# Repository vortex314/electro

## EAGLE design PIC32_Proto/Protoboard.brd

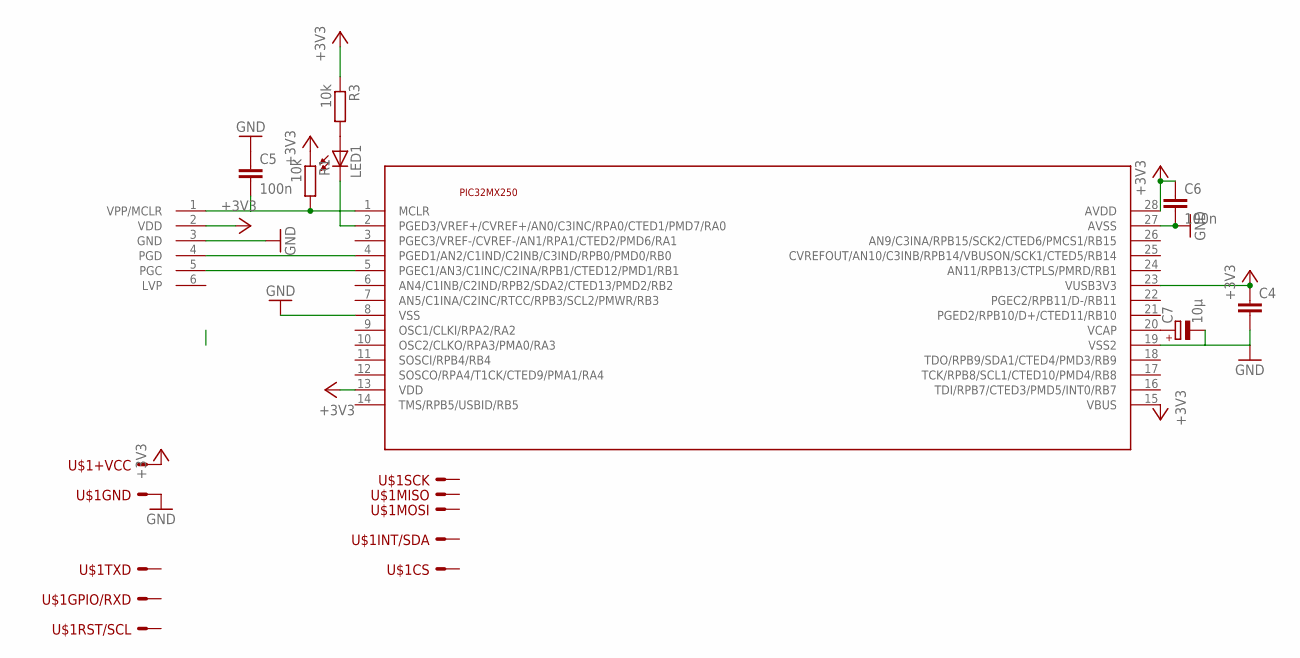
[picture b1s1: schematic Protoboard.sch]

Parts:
C4: C-EU050-025X075; C050-025X075
C5: 100n; C050-025X075
C6: 100n; C050-024X044
C7: 10µ; E1,8-4
LED1: LED5MM
R1, R3: 10k; 0207/10
U$1: SPI_BUS2
U$2: ICSP-6_6P; 1X06-CLEANBIG
U$3: PIC32MX2XXSOIC; SOIC28

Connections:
+3V3: C4.1, C6.1, R1.1, R3.1, U$1.+VCC, U$2.2 (VDD), U$3.13 (VDD), U$3.15 (VBUS), U$3.23 (VUSB3V3), U$3.28 (AVDD)
GND: C4.2, C5.1, C6.2, C7.-, U$1.GND, U$2.3 (GND), U$3.8 (VSS), U$3.19 (VSS2), U$3.27 (AVSS)
unnamed: C5.2, R1.2, U$2.1 (VPP/MCLR), U$3.1 (MCLR)
unnamed: U$2.5 (PGC), U$3.5 (PGEC1/AN3/C1INC/C2INA/RPB1/CTED12/PMD1/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)
unnamed: U$2.4 (PGD), U$3.4 (PGED1/AN2/C1IND/C2INB/C3IND/RPB0/PMD0/R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)
unnamed: LED1.K (C), U$3.2 (PGED3/VREF+/CVREF+/AN0/C3INC/RPA0/CTED1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)
unnamed: C7.+, U$3.20 (VCAP)
unnamed: LED1.A, R3.2

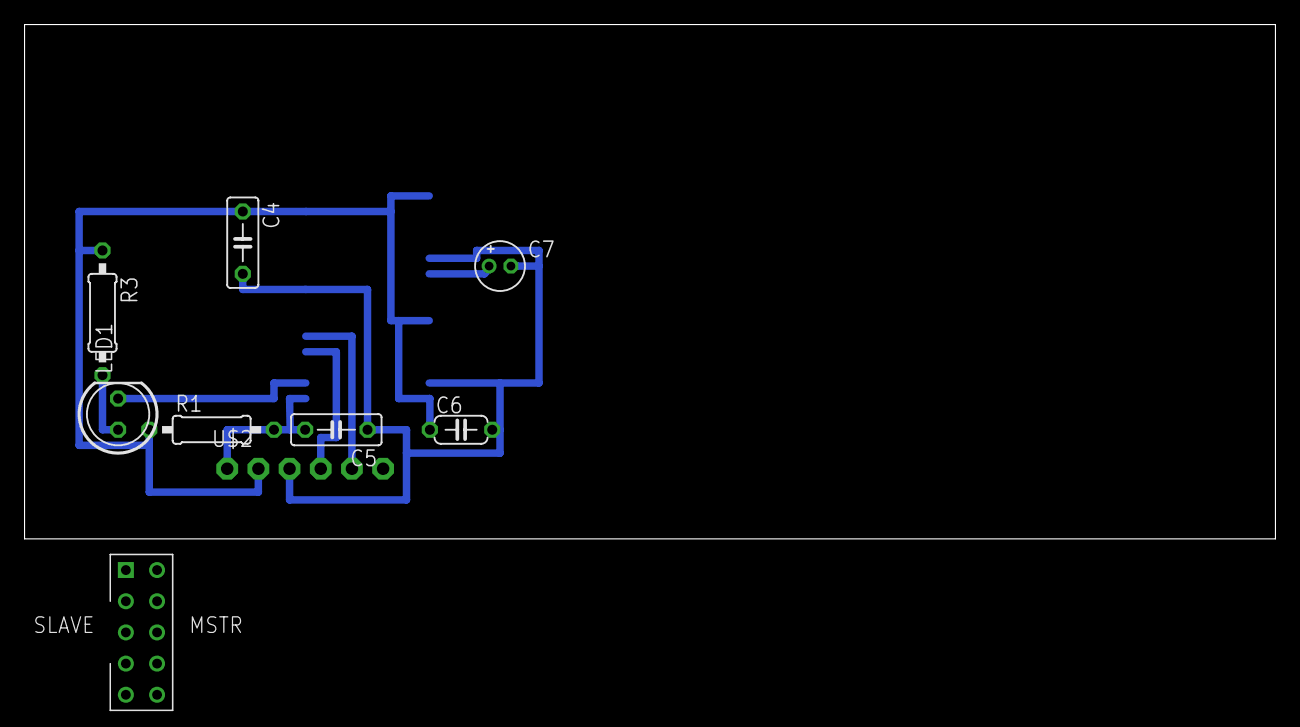
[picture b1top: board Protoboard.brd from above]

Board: 2 copper layers, 101.9 x 41.9 mm, 10 parts (1 on the bottom side), 8 nets.

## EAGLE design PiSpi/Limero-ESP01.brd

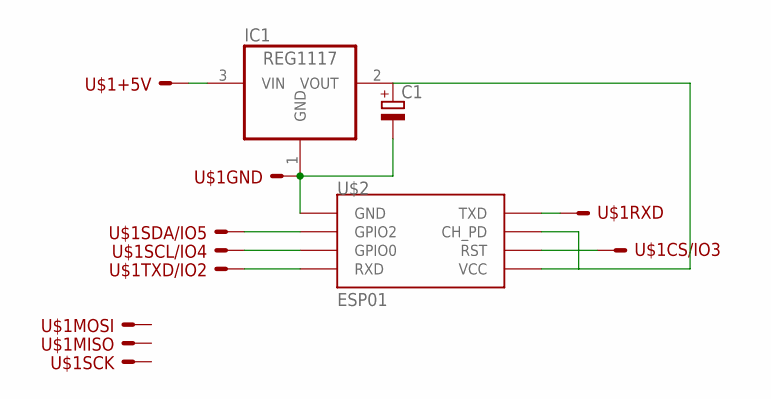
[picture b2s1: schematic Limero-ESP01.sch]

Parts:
C1: CPOL-EUB45181A; B45181A
IC1: REG1117; SOT223
U$1: LIMERO_BUS; SPI_BUS
U$2: ESP01

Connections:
unnamed: C1.-, IC1.1 (GND), U$1.GND, U$2.GND
unnamed: U$1.TXD, U$2.RX (RXD)
unnamed: U$1.RXD, U$2.TX (TXD)
unnamed: U$1.CS, U$2.RST
unnamed: U$1.SCL, U$2.GPIO0
unnamed: U$1.SDA, U$2.GPIO2
unnamed: IC1.3 (VIN), U$1.+5V
unnamed: C1.+, IC1.2 (VOUT), U$2.CH_PD, U$2.VCC

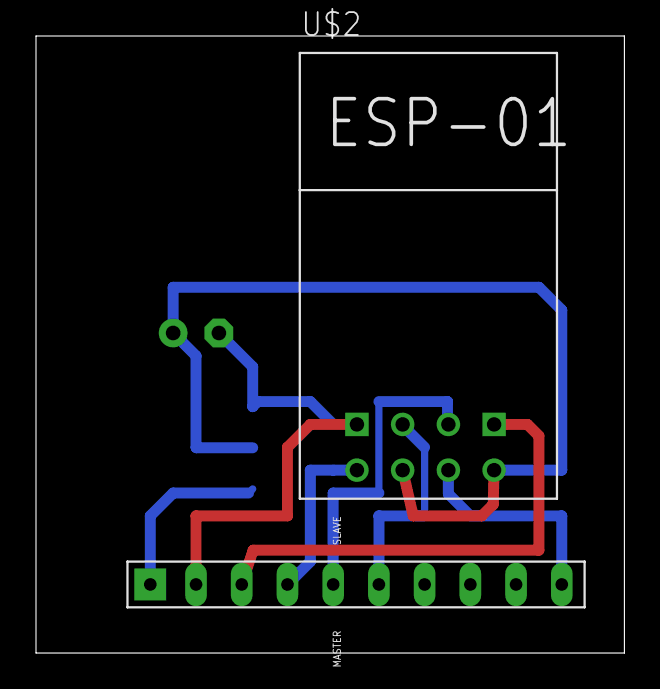
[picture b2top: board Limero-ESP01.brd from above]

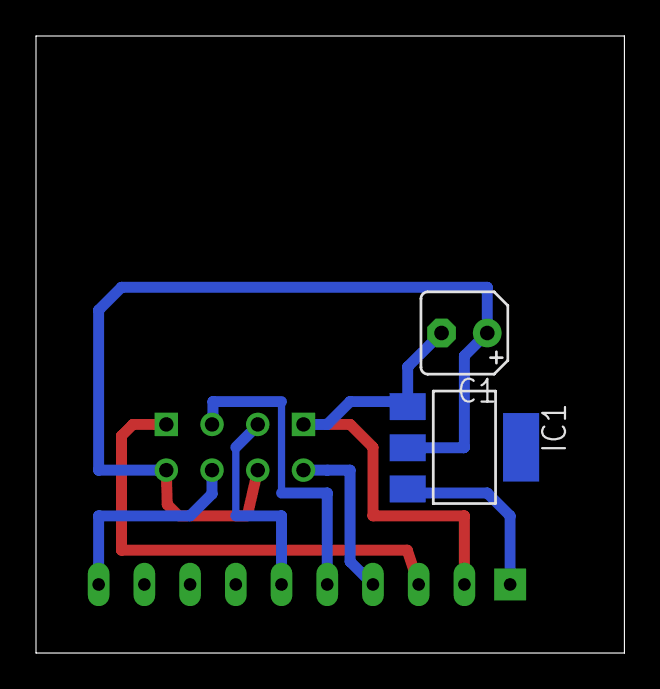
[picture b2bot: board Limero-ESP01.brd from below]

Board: 2 copper layers, 32.7 x 34.3 mm, 4 parts (2 on the bottom side), 8 nets.

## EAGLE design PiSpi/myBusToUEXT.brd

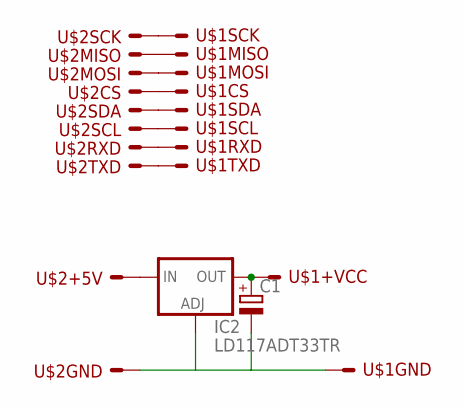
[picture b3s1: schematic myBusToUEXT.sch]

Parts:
C1: CPOL-EUE2.5-5; E2,5-5
IC2: LD117ADT33TR; DPACK
U$1: SPI_BUS2
U$2: SPI_BUS

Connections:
unnamed: U$1.TXD, U$2.TXD
unnamed: U$1.MOSI, U$2.MOSI
unnamed: U$1.MISO, U$2.MISO
unnamed: U$1.SCK, U$2.SCK
unnamed: U$1.CS, U$2.CS
unnamed: U$1.INT/SDA, U$2.SDA
unnamed: U$1.RST/SCL, U$2.SCL
unnamed: U$1.GPIO/RXD, U$2.RXD
unnamed: C1.-, IC2.1 (ADJ), U$1.GND, U$2.GND
unnamed: C1.+, IC2.4 (OUT), U$1.+VCC
unnamed: IC2.3 (IN), U$2.+5V

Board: 2 copper layers, 4 parts (1 on the bottom side), 11 nets, no tracks yet.

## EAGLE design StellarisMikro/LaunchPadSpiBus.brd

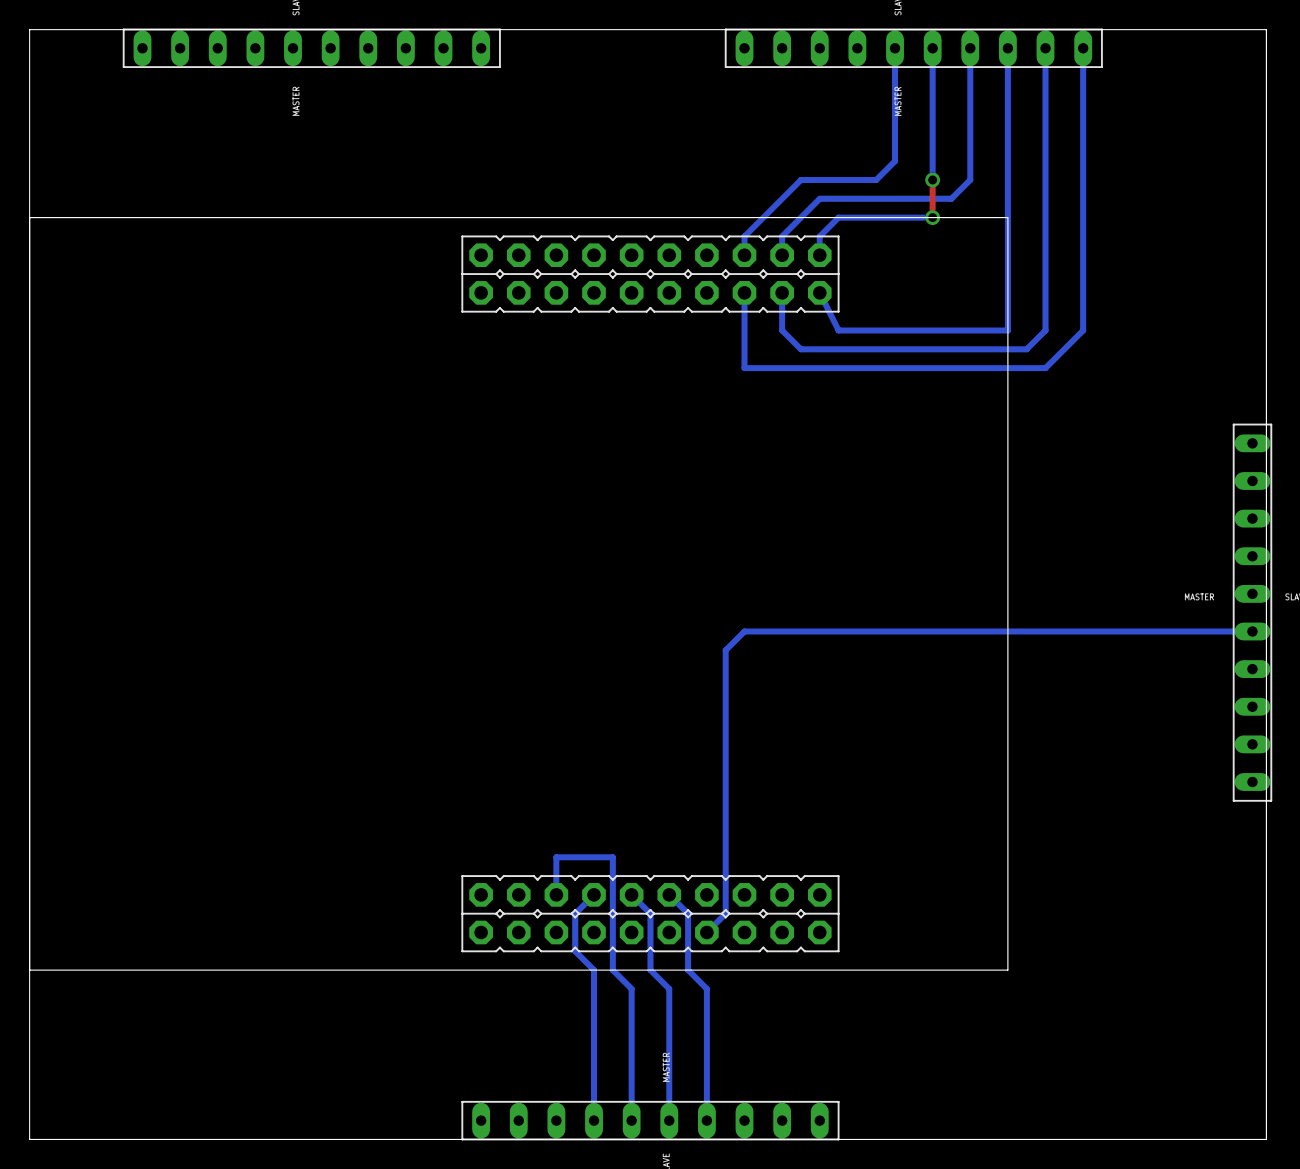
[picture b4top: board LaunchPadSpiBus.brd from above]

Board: 2 copper layers, 83.5 x 74.9 mm, 5 parts (0 on the bottom side), 22 nets.

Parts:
U$1: STELLARIS-LAUNCHPADSTELLARIS-LAUNCHPAD-XL; LAUNCHPAD-XL
U$2, U$3, U$4, U$5: SPI_BUS

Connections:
unnamed: U$1.PA3, U$2.CS
unnamed: U$1.PD0, U$3.SCK
unnamed: U$1.PD1, U$3.CS
unnamed: U$1.VBUS, U$2.+5V, U$3.+5V
unnamed: U$1.PA2, U$2.SCK
unnamed: U$1.GND1, U$1.GND2, U$2.GND, U$3.GND
unnamed: U$1.3.3V, U$2.+3V3, U$3.+3V3
unnamed: U$1.PB5, U$5.CS
unnamed: U$1.PA5, U$2.MOSI
unnamed: U$1.PB4, U$5.SCK
unnamed: U$1.PB7, U$5.MOSI
unnamed: U$1.PB6, U$5.MISO
unnamed: U$1.PA4, U$2.MISO
unnamed: U$1.PF4, U$2.INT
unnamed: U$1.PD7, U$2.RST
unnamed: U$1.PD6, U$2.GPIO
unnamed: U$1.PD2, U$3.MISO
unnamed: U$1.PD3, U$3.MOSI
unnamed: U$1.PF1, U$4.MOSI
unnamed: U$1.PF0, U$4.MISO
unnamed: U$1.PF2, U$4.SCK
unnamed: U$1.PF3, U$4.CS

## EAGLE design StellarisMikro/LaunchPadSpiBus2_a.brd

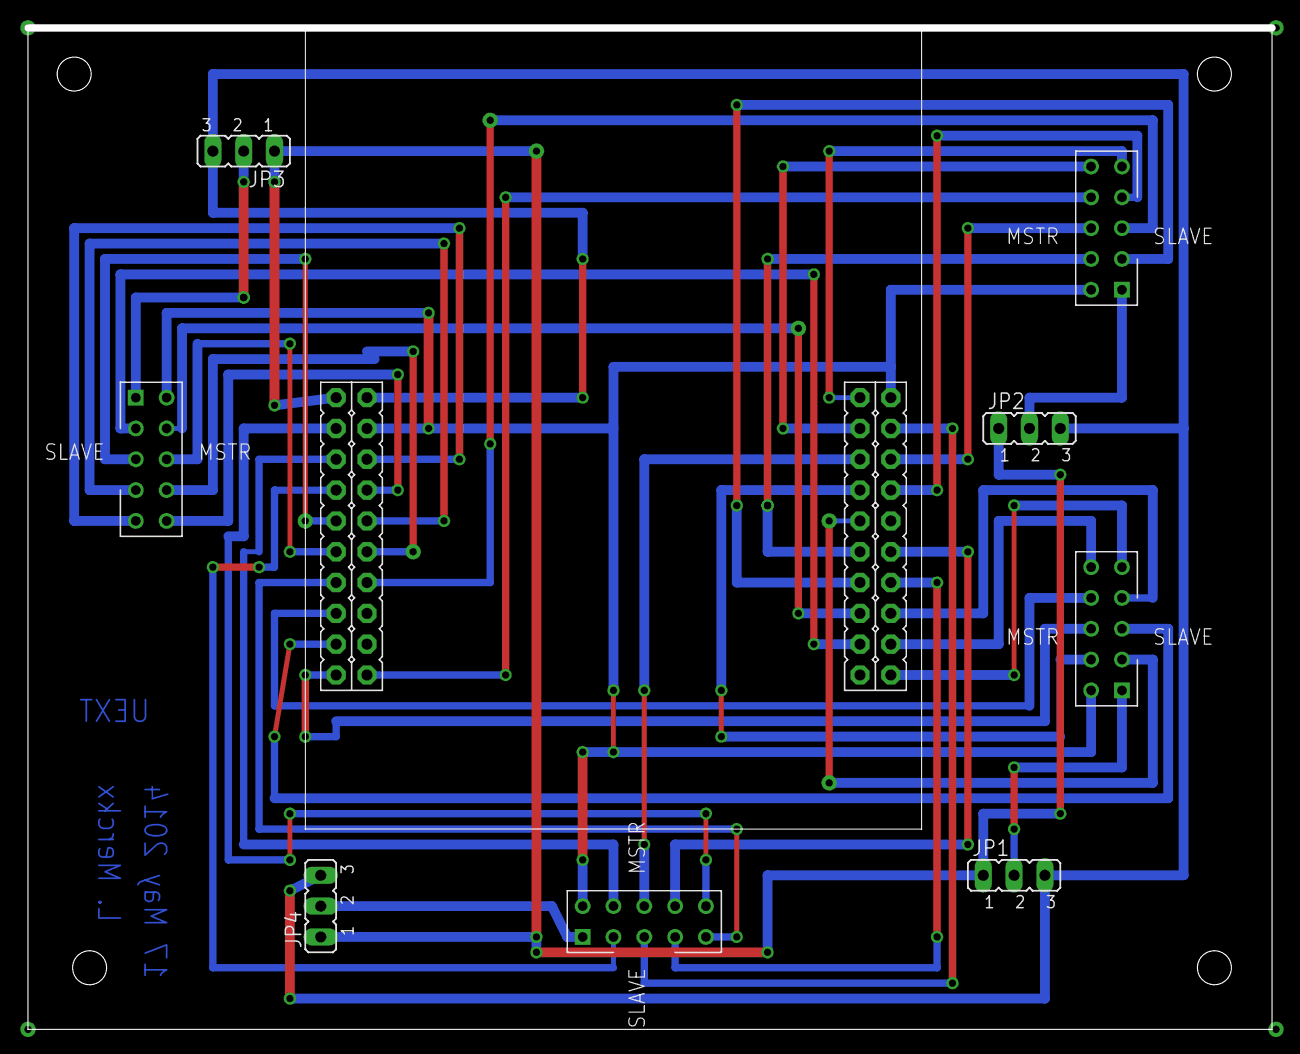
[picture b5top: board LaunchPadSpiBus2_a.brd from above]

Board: 2 copper layers, 102.5 x 82.5 mm, 9 parts (0 on the bottom side), 39 nets.

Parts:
JP1, JP2, JP3, JP4: JP2
U$1: STELLARIS-LAUNCHPADSTELLARIS-LAUNCHPAD-XL; LAUNCHPAD-XL
U$2, U$3, U$4, U$5: SPI_BUS2

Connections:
+3V3: JP1.1, JP2.1, JP3.1, JP4.1, U$1.3.3V
+5V: JP1.3, JP2.3, JP3.3, JP4.3, U$1.VBUS
unnamed: U$1.PA2, U$2.SCK
unnamed: U$1.PA4, U$2.MISO
unnamed: U$1.PA5, U$2.MOSI
unnamed: U$1.PA3, U$2.CS
unnamed: U$1.PC5, U$2.TXD
unnamed: JP1.2, U$2.+VCC
unnamed: U$1.GND1, U$1.GND2, U$2.GND, U$3.GND, U$4.GND, U$5.GND
unnamed: U$1.PF2, U$3.SCK
unnamed: U$1.PF0, U$3.MISO
unnamed: U$1.PF1, U$3.MOSI
unnamed: U$1.PF3, U$3.CS
unnamed: U$1.PD0, U$4.SCK
unnamed: U$1.PD2, U$4.MISO
unnamed: U$1.PD3, U$4.MOSI
unnamed: U$1.PD1, U$4.CS
unnamed: U$1.PB5, U$5.CS
unnamed: U$1.PB6, U$5.MISO
unnamed: U$1.PB7, U$5.MOSI
unnamed: U$1.PB4, U$5.SCK
unnamed: U$1.PA6, U$2.RST/SCL
unnamed: U$1.PA7, U$2.INT/SDA
unnamed: U$1.PC4, U$2.GPIO/RXD
unnamed: U$1.PB3, U$5.INT/SDA
unnamed: U$1.PB0, U$5.GPIO/RXD
unnamed: U$1.PB2, U$5.RST/SCL
unnamed: U$1.PB1, U$5.TXD
unnamed: U$1.PD6, U$4.GPIO/RXD
unnamed: U$1.PD7, U$4.TXD
unnamed: U$1.PE4, U$4.RST/SCL
unnamed: U$1.PE5, U$4.INT/SDA
unnamed: U$1.PC6, U$3.GPIO/RXD
unnamed: U$1.PC7, U$3.TXD
unnamed: U$1.PE0, U$3.INT/SDA
unnamed: U$1.PE1, U$3.RST/SCL
unnamed: JP2.2, U$3.+VCC
unnamed: JP3.2, U$4.+VCC
unnamed: JP4.2, U$5.+VCC

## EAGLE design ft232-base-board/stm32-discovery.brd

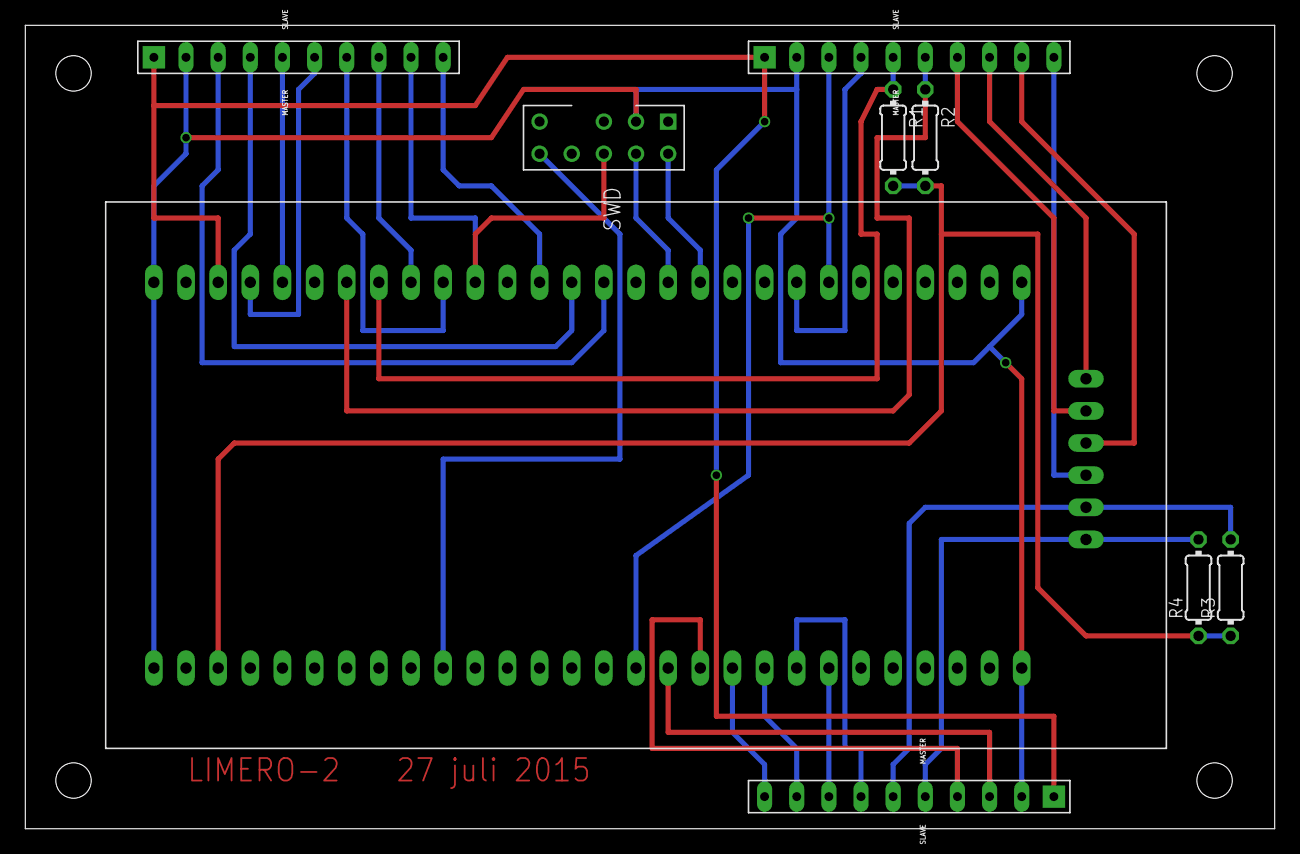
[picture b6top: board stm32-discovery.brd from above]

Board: 2 copper layers, 98.7 x 63.5 mm, 9 parts (0 on the bottom side), 30 nets.

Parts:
R1, R2, R3, R4: 0204/7
U$1: STM32_DISCOVERY
U$2, U$3, U$5: SPI_BUS
U$4: SWD

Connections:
unnamed: U$1.PA2, U$3.TXD
unnamed: U$1.PA3, U$3.RXD
unnamed: U$1.GND@1, U$1.GND@2, U$1.GND@3, U$1.GND@4, U$2.GND, U$3.GND, U$4.GND, U$5.GND
unnamed: U$1.5V, U$2.+5V, U$3.+5V, U$5.+5V
unnamed: U$1.PA4, U$3.CS
unnamed: U$1.PA5, U$3.SCK
unnamed: U$1.PA6, U$3.MISO
unnamed: U$1.PA7, U$3.MOSI
unnamed: R4.2, U$1.PB10, U$3.SCL
unnamed: R3.2, U$1.PB11, U$3.SDA
unnamed: U$1.PA1, U$1.PA9, U$2.TXD
unnamed: U$1.PA10, U$2.RXD
unnamed: U$1.PB12, U$2.CS
unnamed: U$1.PB13, U$2.SCK
unnamed: U$1.PB14, U$2.MISO
unnamed: U$1.PB15, U$2.MOSI
unnamed: R1.1, U$1.PB6, U$2.SCL
unnamed: R2.1, U$1.PB7, U$2.SDA
unnamed: U$1.PA13, U$4.SWDIO
unnamed: U$1.PA14, U$4.SWCLK
unnamed: U$1.RST, U$4.RST
unnamed: U$1.PB3, U$4.SWO, U$5.SCK
unnamed: U$1.PB8, U$5.SCL
unnamed: U$1.PB9, U$5.SDA
unnamed: U$1.PC10, U$5.TXD
unnamed: U$1.PC11, U$5.RXD
unnamed: U$1.PB4, U$5.MISO
unnamed: U$1.PB5, U$5.MOSI
unnamed: U$1.PC12, U$5.CS
VCC: R1.2, R2.2, R3.1, R4.1, U$1.3V3
